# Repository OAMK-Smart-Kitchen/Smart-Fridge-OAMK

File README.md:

# Smart-Fridge-OAMK
The first project of the 'Smart Kitchen' commissioned by OAMK University of Applied Sciences in Oulu - Finland.

The concept: [Prezi](http://prezi.com/kkwk0fvxtakd/?utm_campaign=share&utm_medium=copy&rc=ex0share)
The Moqups: [Moqups](https://moqups.com/berndv/YKEUgVQ0)

Dedicated to Tom Mampaey and Bernd Verhofstadt (Erasmus students from Belgium) by:

### Contactpersons Finland:
#### Mr. Jussi Kangasoja
Email: Jussi.Kangasoja@oamk.fi

#### Ms. Kaisa Orajärvi
Email: kaisa.orajarvi@oamk.fi

### Contactperson Belgium:
#### Mr. Jeroen Doggen
Email: jeroen.doggen@ap.be

Github: [github.com/jeroendoggen](https://github.com/jeroendoggen)

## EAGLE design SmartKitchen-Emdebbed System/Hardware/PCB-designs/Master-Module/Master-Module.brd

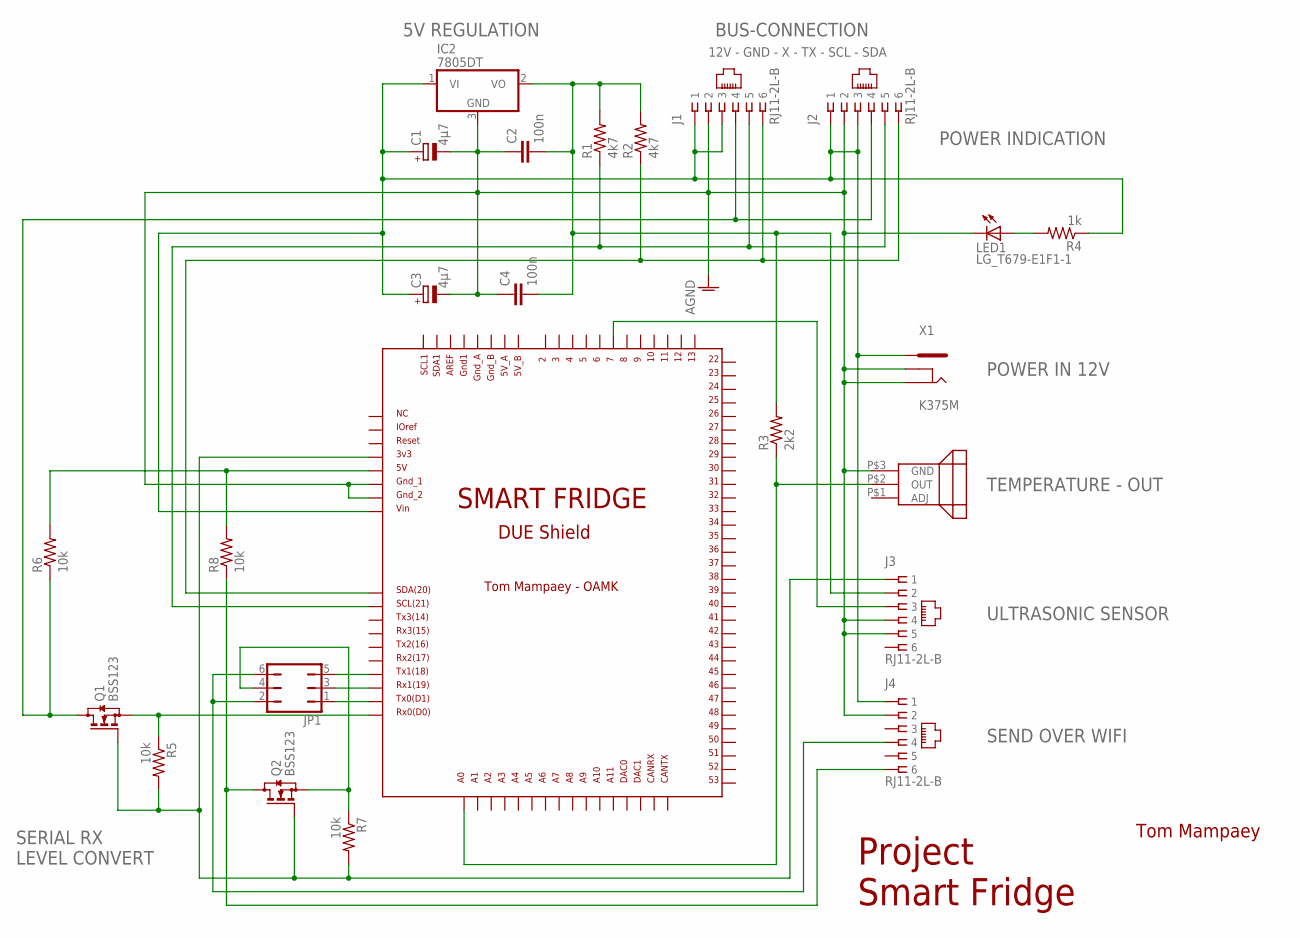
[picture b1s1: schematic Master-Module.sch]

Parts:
C1, C3: 4µ7; PANASONIC_B
C2, C4: 100n; C0603
IC2: 7805DT; TO252
J1, J2, J3: RJ11-2L-B; RJ11-NO_SHIELD
J4: RJ11-2L-B; RJ11-NO_SHIELD; MPN RJ11-2L-B
JP1: JP3Q
LED1: LG_T679-E1F1-1; PLCC2
Q1, Q2: BSS123; SOT23
R1, R2: 4k7; R0402
R3: 2k2; R0402
R4: 1k; R0402
R5, R6, R7, R8: 10k; R0402
U$1: DUE(NORMAL)
U$2: LM335
X1: K375M

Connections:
AGND: C1.-, C2.1, C3.-, C4.1, IC2.3 (GND), J1.2, J2.2, J3.4, J3.5, J4.2, LED1.C, U$1.GND_1, U$1.GND_2, U$2.P$3 (GND), X1.P$1 (2), X1.P$6 (3)
unnamed: J1.6, J2.6, R2.1, U$1.SDA
unnamed: J1.4, J2.4, Q1.3 (D), R6.1
unnamed: J1.5, J2.5, R1.1, U$1.SCL
unnamed: R6.2, R8.2, U$1.5V
unnamed: R3.1, U$1.A0, U$2.P$2 (OUT)
unnamed: J3.3, U$1.7
unnamed: LED1.A, R4.2
unnamed: C2.2, C4.2, IC2.2 (VO), J3.2, R1.2, R2.2, R3.2
unnamed: Q1.2 (S), R5.1, U$1.RX0
unnamed: JP1.1, U$1.TX0
unnamed: J3.1, Q1.1 (G), Q2.1 (G), R5.2, R7.2, U$1.3V3
unnamed: JP1.3, U$1.RX1
unnamed: JP1.5, U$1.TX1
unnamed: J4.4, JP1.2, JP1.6
unnamed: J4.6, Q2.3 (D), R8.1
unnamed: JP1.4, Q2.2 (S), R7.1
unnamed: C1.+, C3.+, IC2.1 (VI), J1.1, J1.3, J2.1, J2.3, J4.1, R4.1, U$1.VIN, X1.P$7 (1)

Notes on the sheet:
12V - GND - X - TX - SCL - SDA
BUS-CONNECTION
5V REGULATION
POWER IN 12V
ULTRASONIC SENSOR
TEMPERATURE - OUT
Tom Mampaey
Project Smart Fridge
POWER INDICATION
SERIAL RX LEVEL CONVERT
SEND OVER WIFI

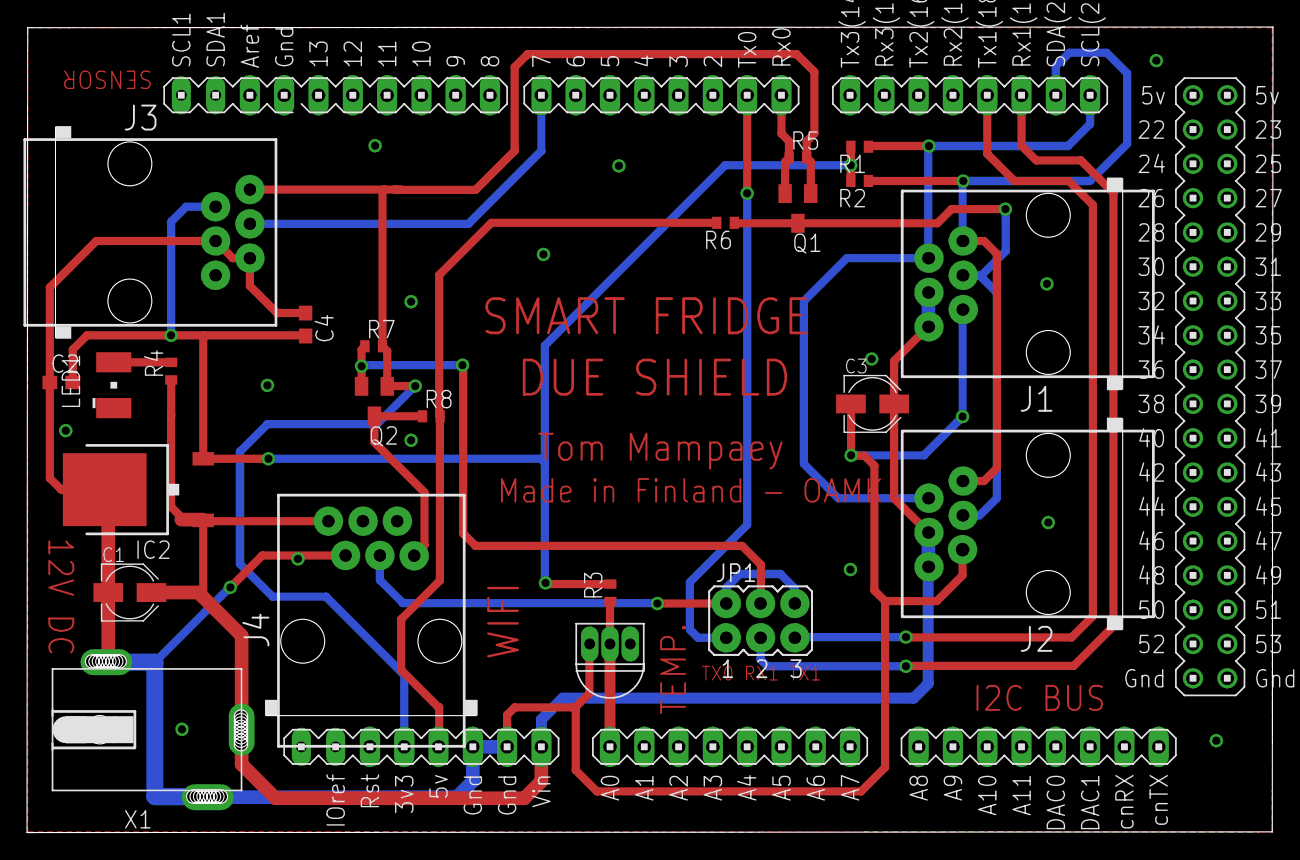
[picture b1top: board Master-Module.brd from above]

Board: 2 copper layers, 92.3 x 59.7 mm, 24 parts (0 on the bottom side), 18 nets.

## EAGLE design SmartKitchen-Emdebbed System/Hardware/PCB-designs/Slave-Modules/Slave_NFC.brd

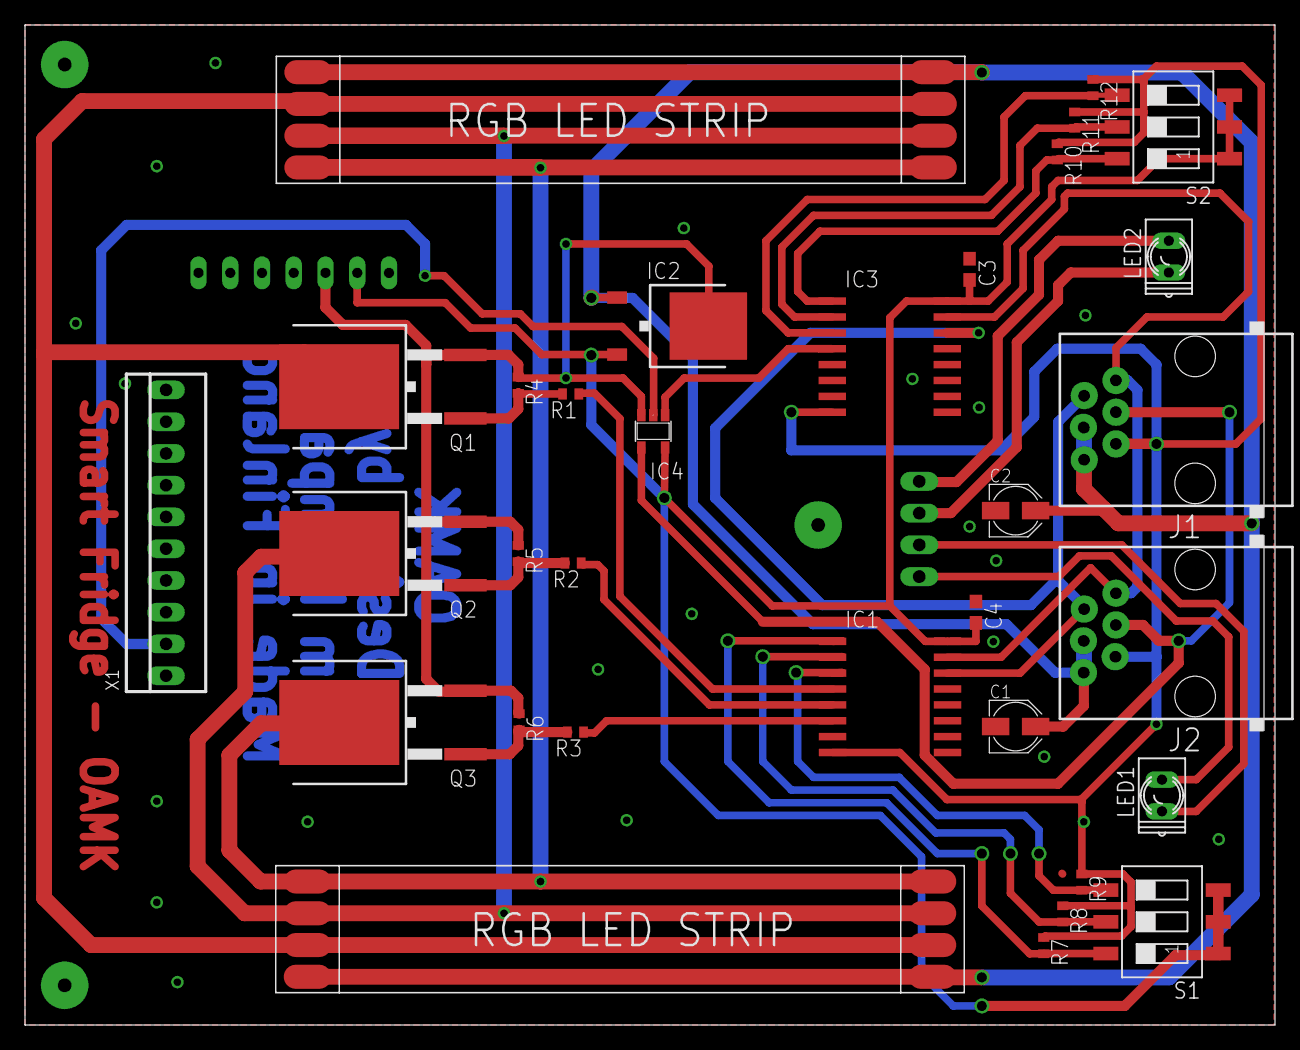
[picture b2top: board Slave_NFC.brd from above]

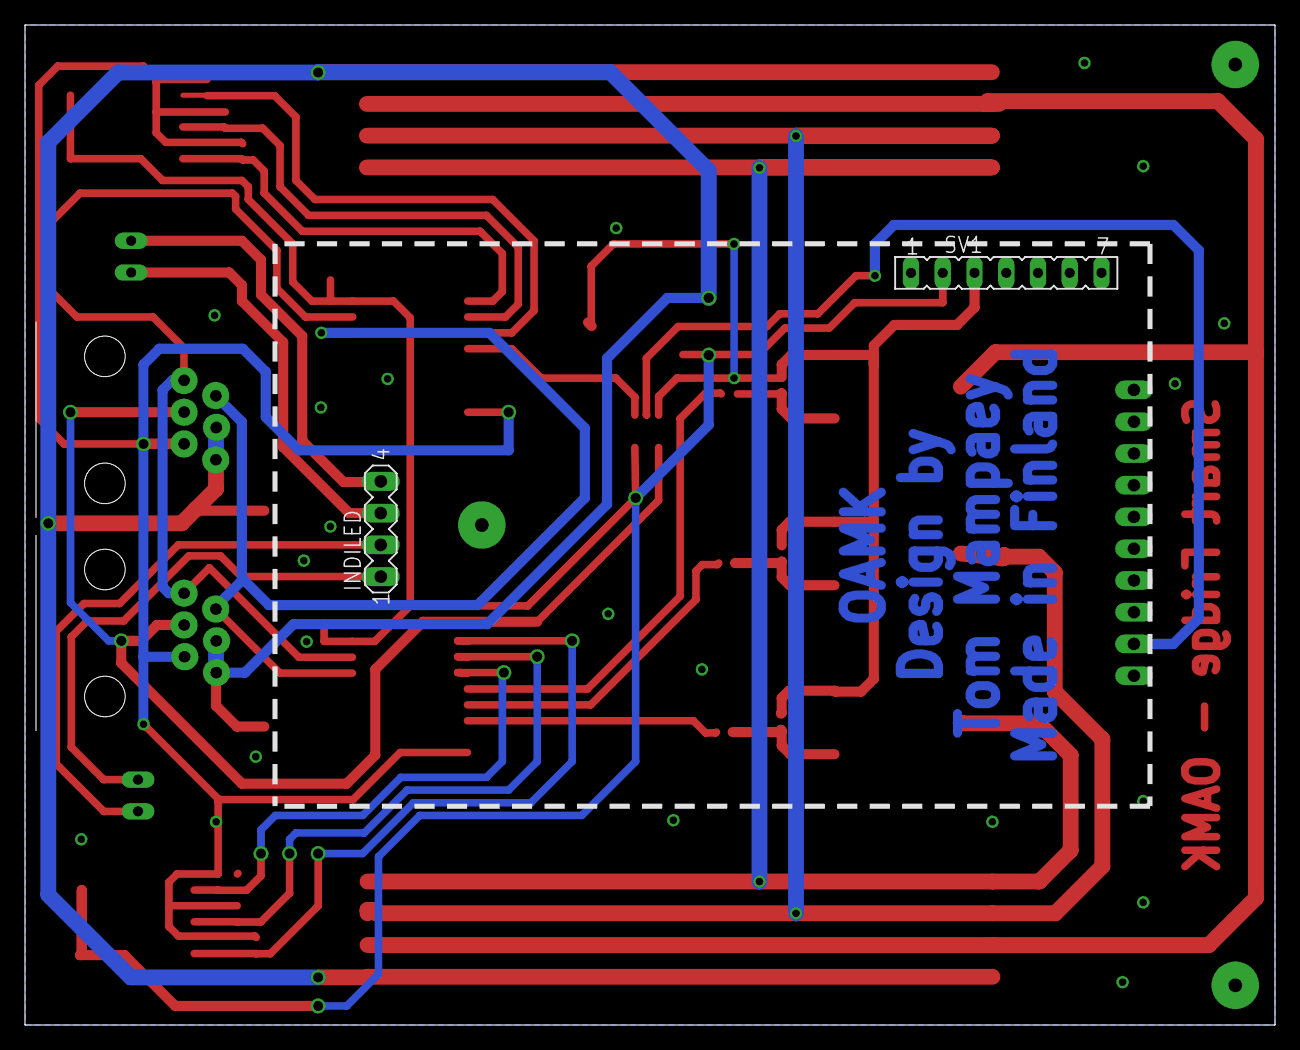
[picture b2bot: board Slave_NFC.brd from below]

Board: 2 copper layers, 100.0 x 80.0 mm, 34 parts (2 on the bottom side), 27 nets.

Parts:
C1, C2: 4µ7; PANASONIC_B
C3, C4: 100n; C0603
IC1, IC3: PCF8574T; SO16W
IC2: 7805DT; TO252
IC4: 74AHC1G126DBV; SOT23-5
INDILED: MA04-1
J1, J2: RJ11-2L-B; RJ11-NO_SHIELD
LED1, LED2: Q62902-B152
Q1, Q2, Q3: SPB80P06P; TO263
R1, R2, R3: 10Ω; R0402
R4, R5, R6: 2.7MΩ; R0402
R7, R8, R9, R10, R11, R12: 4k7; R0402
S1, S2: SWS003; SMS-003
SV1: FE07
U$1, U$2: LED_S; LED_P
X1: 22-23-2101

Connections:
AGND: C1.-, C2.-, C3.1, C4.1, IC1.8, IC2.3, IC3.8, IC4.3, J1.2, J2.2, Q1.2, Q2.2, Q3.2, R4.1, R5.1, R6.1, R7.1, R8.1, R9.1, R10.1, R11.1, R12.1, SV1.3
unnamed: IC1.15, IC3.15, J1.6, J2.6
unnamed: IC4.4, J1.4, J2.4
unnamed: IC1.14, IC3.14, J1.5, J2.5
unnamed: Q1.1, R1.2, R4.2
unnamed: Q2.1, R2.2, R5.2
unnamed: Q3.1, R3.2, R6.2
unnamed: Q1.3, U$1.B, U$1.B1, U$2.B, U$2.B1
unnamed: Q2.3, U$1.R, U$1.R1, U$2.R, U$2.R1
unnamed: Q3.3, U$1.G, U$1.G1, U$2.G, U$2.G1
unnamed: C1.+, C2.+, IC2.1, J1.1, J1.3, J2.1, J2.3, U$1.+, U$1.+1, U$2.+, U$2.+1
unnamed: IC3.1, R10.2, S2.6
unnamed: IC1.1, R7.2, S1.6
unnamed: IC1.2, R8.2, S1.5
unnamed: IC1.3, R9.2, S1.4
unnamed: IC3.4, IC4.1
unnamed: IC1.4, R1.1
unnamed: IC1.5, R2.1
unnamed: IC1.6, R3.1
unnamed: IC3.2, R11.2, S2.5
unnamed: IC3.3, R12.2, S2.4
unnamed: C3.2, C4.2, IC1.16, IC2.2, IC3.16, IC4.5, S1.1, S1.2, S1.3, S2.1, S2.2, S2.3, SV1.2
unnamed: INDILED.1, LED1.A
unnamed: INDILED.4, LED2.A
unnamed: INDILED.2, LED1.K
unnamed: INDILED.3, LED2.K
unnamed: IC4.2, X1.2

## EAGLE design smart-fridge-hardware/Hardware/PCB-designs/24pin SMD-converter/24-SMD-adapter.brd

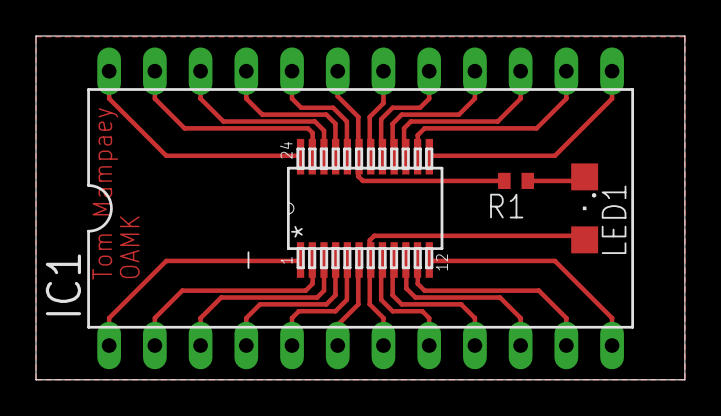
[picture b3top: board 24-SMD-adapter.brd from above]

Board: 2 copper layers, 36.0 x 19.1 mm, 4 parts (0 on the bottom side), 25 nets.

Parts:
IC1: DIL24-6
LED1: SML1206
R1: R0402
_: SC16IS750; SOT361_1_M

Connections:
unnamed: IC1.1, _.1
unnamed: IC1.2, _.2
unnamed: IC1.3, _.3
unnamed: IC1.4, _.4
unnamed: IC1.5, _.5
unnamed: IC1.6, _.6
unnamed: IC1.7, LED1.A, _.7
unnamed: IC1.8, _.8
unnamed: IC1.9, _.9
unnamed: IC1.10, _.10
unnamed: IC1.11, _.11
unnamed: IC1.12, _.12
unnamed: IC1.24, _.24
unnamed: IC1.23, _.23
unnamed: IC1.22, _.22
unnamed: IC1.21, _.21
unnamed: IC1.20, _.20
unnamed: IC1.19, R1.2, _.19
unnamed: IC1.18, _.18
unnamed: IC1.17, _.17
unnamed: IC1.16, _.16
unnamed: IC1.15, _.15
unnamed: IC1.14, _.14
unnamed: IC1.13, _.13
unnamed: LED1.C, R1.1

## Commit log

2015-01-15 :confetti_ball: Added .gitattributes
2015-01-15 Starting the first documents.
2015-01-15 adding tree
2015-01-15 Added folders
2015-01-15 adding information to report
    introduction, the project and githublink
2015-01-15 Added project description (outline)
2015-01-15 Adding user recognition options
2015-01-21 Finished Concept Report and added Gantt-chart
2015-01-22 Updated Readme File Fixes #1
2015-01-22 Update README.md Layout
2015-01-28 4D-Datasheets
2015-01-30 Added concept press
2015-02-09 Added Estimated needs
2015-02-24 A lot of testing and research
    NFC, I2C, SMD, Serial,...
2015-02-24 Testing with NFC-ID's
2015-02-24 Optimized NFC-reading
2015-02-24 Solution reading NFC-tags
2015-02-26 Working code: Serial I2C interface between twe IC's
2015-02-27 PCB: (First) SMD-design adapter/converter
2015-03-07 Added Readme File
2015-03-08 Added First page with routing
2015-03-08 Added favicons
2015-03-08 Login Layout changed
2015-03-08 Added templates for dasboard and member
2015-03-10 Components, I2C and testcode
2015-03-10 Putting things together
2015-03-11 Layout for dashboard + geolocation weather
2015-03-11 Weather Service added
    Powered by Forecast.io
2015-03-11 Small bug fixed when returning data from weather
2015-03-12 Added I2C_scanner to check addresses and operation
2015-03-12 Added Copyright as rootscope
2015-03-12 Buggy can't show ng-repeat weather
2015-03-12 Weather is displayed on dashboard!
2015-03-12 Weather format changed
2015-03-18 testing the NFC with the ledstrips
2015-03-24 Coding and PCB-design
2015-03-25 Crazy PCB-designings
2015-03-27 Preparation for merge as subtree
2015-04-03 Login and register UI created
2015-04-04 Members UI added
2015-04-04 Title on members page edited
2015-04-04 myProfile UI added
2015-04-05 Empty pages with navigation created
2015-04-05 My Health UI added
2015-04-05 Added slice filer for the weather
    Didn't know that it was deleted...
2015-04-15 Login and Register Feature added!
2015-04-15 BMI and Points template added
2015-04-15 .brd files for SMD-desgin
2015-04-15 Renamed Embedded system
2015-04-15 Code cleanup
2015-04-15 All members + Active Member in scope
2015-04-15 active member not shown on menu
2015-04-15 Testsoftware + Fix problem wire
2015-04-16 fixes frontpage button responsive style
2015-04-16 Member is shown when logged in
2015-04-16 Download lib in solution
2015-04-16 Login required for pages
2015-04-16 Active membername displayed on dashboard
2015-04-16 Play sound in dashboard + navigation changed
2015-04-17 Testing software I2C on PCB's
2015-04-17 Hard time finding performant algorithm NFC-ID
2015-04-19 Comparing tag-ID's
2015-04-20 BootboxJS Update
2015-04-20 Working LEDDRIVER over I2C
2015-04-20 Starting new algorithm
2015-04-20 Add Member to family
2015-04-20 Optimized PCB-board 2.0 with header for MAX232
2015-04-20 getting id
2015-04-21 Make the admin visible in the memberlist
2015-04-21 Adding interference capacitors and testingcode
2015-04-21 fixing powerpeaks and nfc-read
2015-04-21 Final PCB-design for NFC-reader modules
    I'm proud
2015-04-21 Adding farnell-list
2015-04-21 adding pull-ups and inh-capacitors to list
2015-04-22 Starting new crazy idea Algo ID
2015-04-22 EUREKA! Crazy breakthrough! Performant algoritm NFC
    char array devided in pieces each step until they are the same!
2015-04-22 Optimized & Comment
2015-04-23 small adjustments
2015-04-23 Clearing buffer after algo
2015-04-23 re-read when new tag detected
2015-04-23 Fin(n)ished algorithm NFC-ID's !!!
2015-04-23 Only play sound when selected member
2015-04-24 Custom shield DUE - Master module
2015-04-24 adding connections
2015-04-24 customizing components
2015-04-24 PCB shield
2015-04-24 sheets
2015-04-25 fixed date error, back to the basics!
2015-04-25 added word Forgot to save changes :/
2015-04-27 Sound on select Member
2015-04-27 Adding stupid level-converter for serial connection
2015-04-27 Finnishing DUE shield
2015-04-27 Fine tunning
2015-04-27 Adding planes and references
2015-04-27 Added Wifi library
2015-04-27 Added Json library
2015-04-27 Added Stream library
2015-04-28 test coding wifi and temp
2015-04-28 placeholder for date twice in html code
2015-04-28 Wifi problems
2015-04-28 testing
2015-04-28 FEED ID, API and M2X Master Key!
2015-04-29 Testcommit after sync-error git
2015-04-30 Testing (new)SoftSerial
2015-04-30 testing serial connection between two DUE's
2015-04-30 coming closer
2015-04-30 Serial connection between Due and Due (test for wifi)
2015-05-02 Complete redesing Master for Wifi-port
2015-05-02 Adding via's
2015-05-02 Final Master PCB-design
2015-05-10 Adding information to report
2015-05-10 Cleaning folders
2015-05-10 Change member info added
2015-05-10 Adding schematic and distribution to report
    all my work
2015-05-10 CV and MAIN-SCHEMATIC added in report
2015-05-11 Redesigned wrong component
2015-05-11 Disco-coding finnaly working I2C colorcontrol
2015-05-11 Working nightrider #awesome
2015-05-11 Adding ack to report!
2015-05-12 Putting read and color code togheter
2015-05-12 Deleted the gamemode option in Myprofile
2015-05-12 Admin email cannot be changed
2015-05-12 DataTables added
2015-05-12 Layout DataTable added to Product page
2015-05-12 coding
2015-05-12 Switch to open serial data modules
2015-05-12 Datatables icon fix
2015-05-12 Products are loaded in table from server
2015-05-13 Adding userdetection and stabelaizing
2015-05-13 return bool for userdetection
2015-05-13 Working Wifitest - connect and read html
2015-05-13 Testing (and succes) Wifi-connection
2015-05-13 Testing first PUT's to server
2015-05-13 options
2015-05-13 Frustrations with PUT to Server
2015-05-13 Figuring out how to put/post to server with mega
2015-05-14 Fixing probels with PUT
2015-05-14 Cleaning Wifi-code and make it variable
2015-05-14 making json data var
2015-05-14 Load exercises and watch one. MyPoints
    Only one video can be viewed...
2015-05-14 Testing Serial connection between Master and bauds
2015-05-14 Before testing filtermethods
2015-05-14 Filtering method on char and detect reliable tags
2015-05-14 Working charbuffer array
2015-05-14 chanching names
2015-05-15 Multiple YT video's can be watched, points check
2015-05-15 Added filter for Data in fridge + autoreload
    The whole frame is reloading, has to be fixed in the future
2015-05-15 Windows App created with WebView for webpage
2015-05-15 Staring on Final code
2015-05-15 Working on the main codes (Wifi and Master)
2015-05-16 Points are stored local and in DB
2015-05-16 Forgot quote after style attr
2015-05-16 Loading button for myprofile + cleanup
2015-05-16 MetroApp Copyright added
2015-05-17 Weight and Lenght added to App
2015-05-17 Alerts for user added
2015-05-17 Fixed issue at register date of birth
2015-05-17 Added Avatars female, boy, girl
2015-05-17 Added Genders with img binding
2015-05-17 Changed navigation after register new kitchen
2015-05-17 Input mask Date Of Birth
2015-05-17 Changed new Array() to []
2015-05-18 BMI calculator added with chart
2015-05-18 Dashboard button added
2015-05-18 Dynamic temp and log out button added
2015-05-18 Weather Forecast Layout update
2015-05-18 fixed issue, after login succeed, fields where red
2015-05-18 Unperformant coding Master
2015-05-18 Light optimalisations Master
2015-05-18 We're getting there! Master code
2015-05-19 Optimalizations and cleanup
2015-05-19 Making the code readable Finals
2015-05-19 deleted scope apply to avoid problems
2015-05-19 Added Screen Mockups
2015-05-19 Communication Master & Wifi
2015-05-19 coding all day, Wifimodule Dynamic PUT
2015-05-19 NICEEE! Succesfull nfc-tag PUT's to server!
2015-05-20 Final conding Final Master before presentation
2015-05-23 Added 3D-design test (3D-print)
2015-06-05 Final 3D-design! ready for printing massproduction
2015-06-07 IOS App added to project
    Not signed!
2015-06-07 Index report and cleaning slave
2015-06-07 Report: Adding subjects and datasheets to annex
2015-06-09 Support for iOS 9 and Swift2
2015-06-10 Adding 'Slave module'-information to report
2015-06-10 Adding extra comment and Master code to report
2015-06-11 Adding Master and Wi-Fi information and code to report
2015-06-12 Backup report and PCB information
2015-06-12 Finalising final report
    proud
2015-06-13 Added Final Report
